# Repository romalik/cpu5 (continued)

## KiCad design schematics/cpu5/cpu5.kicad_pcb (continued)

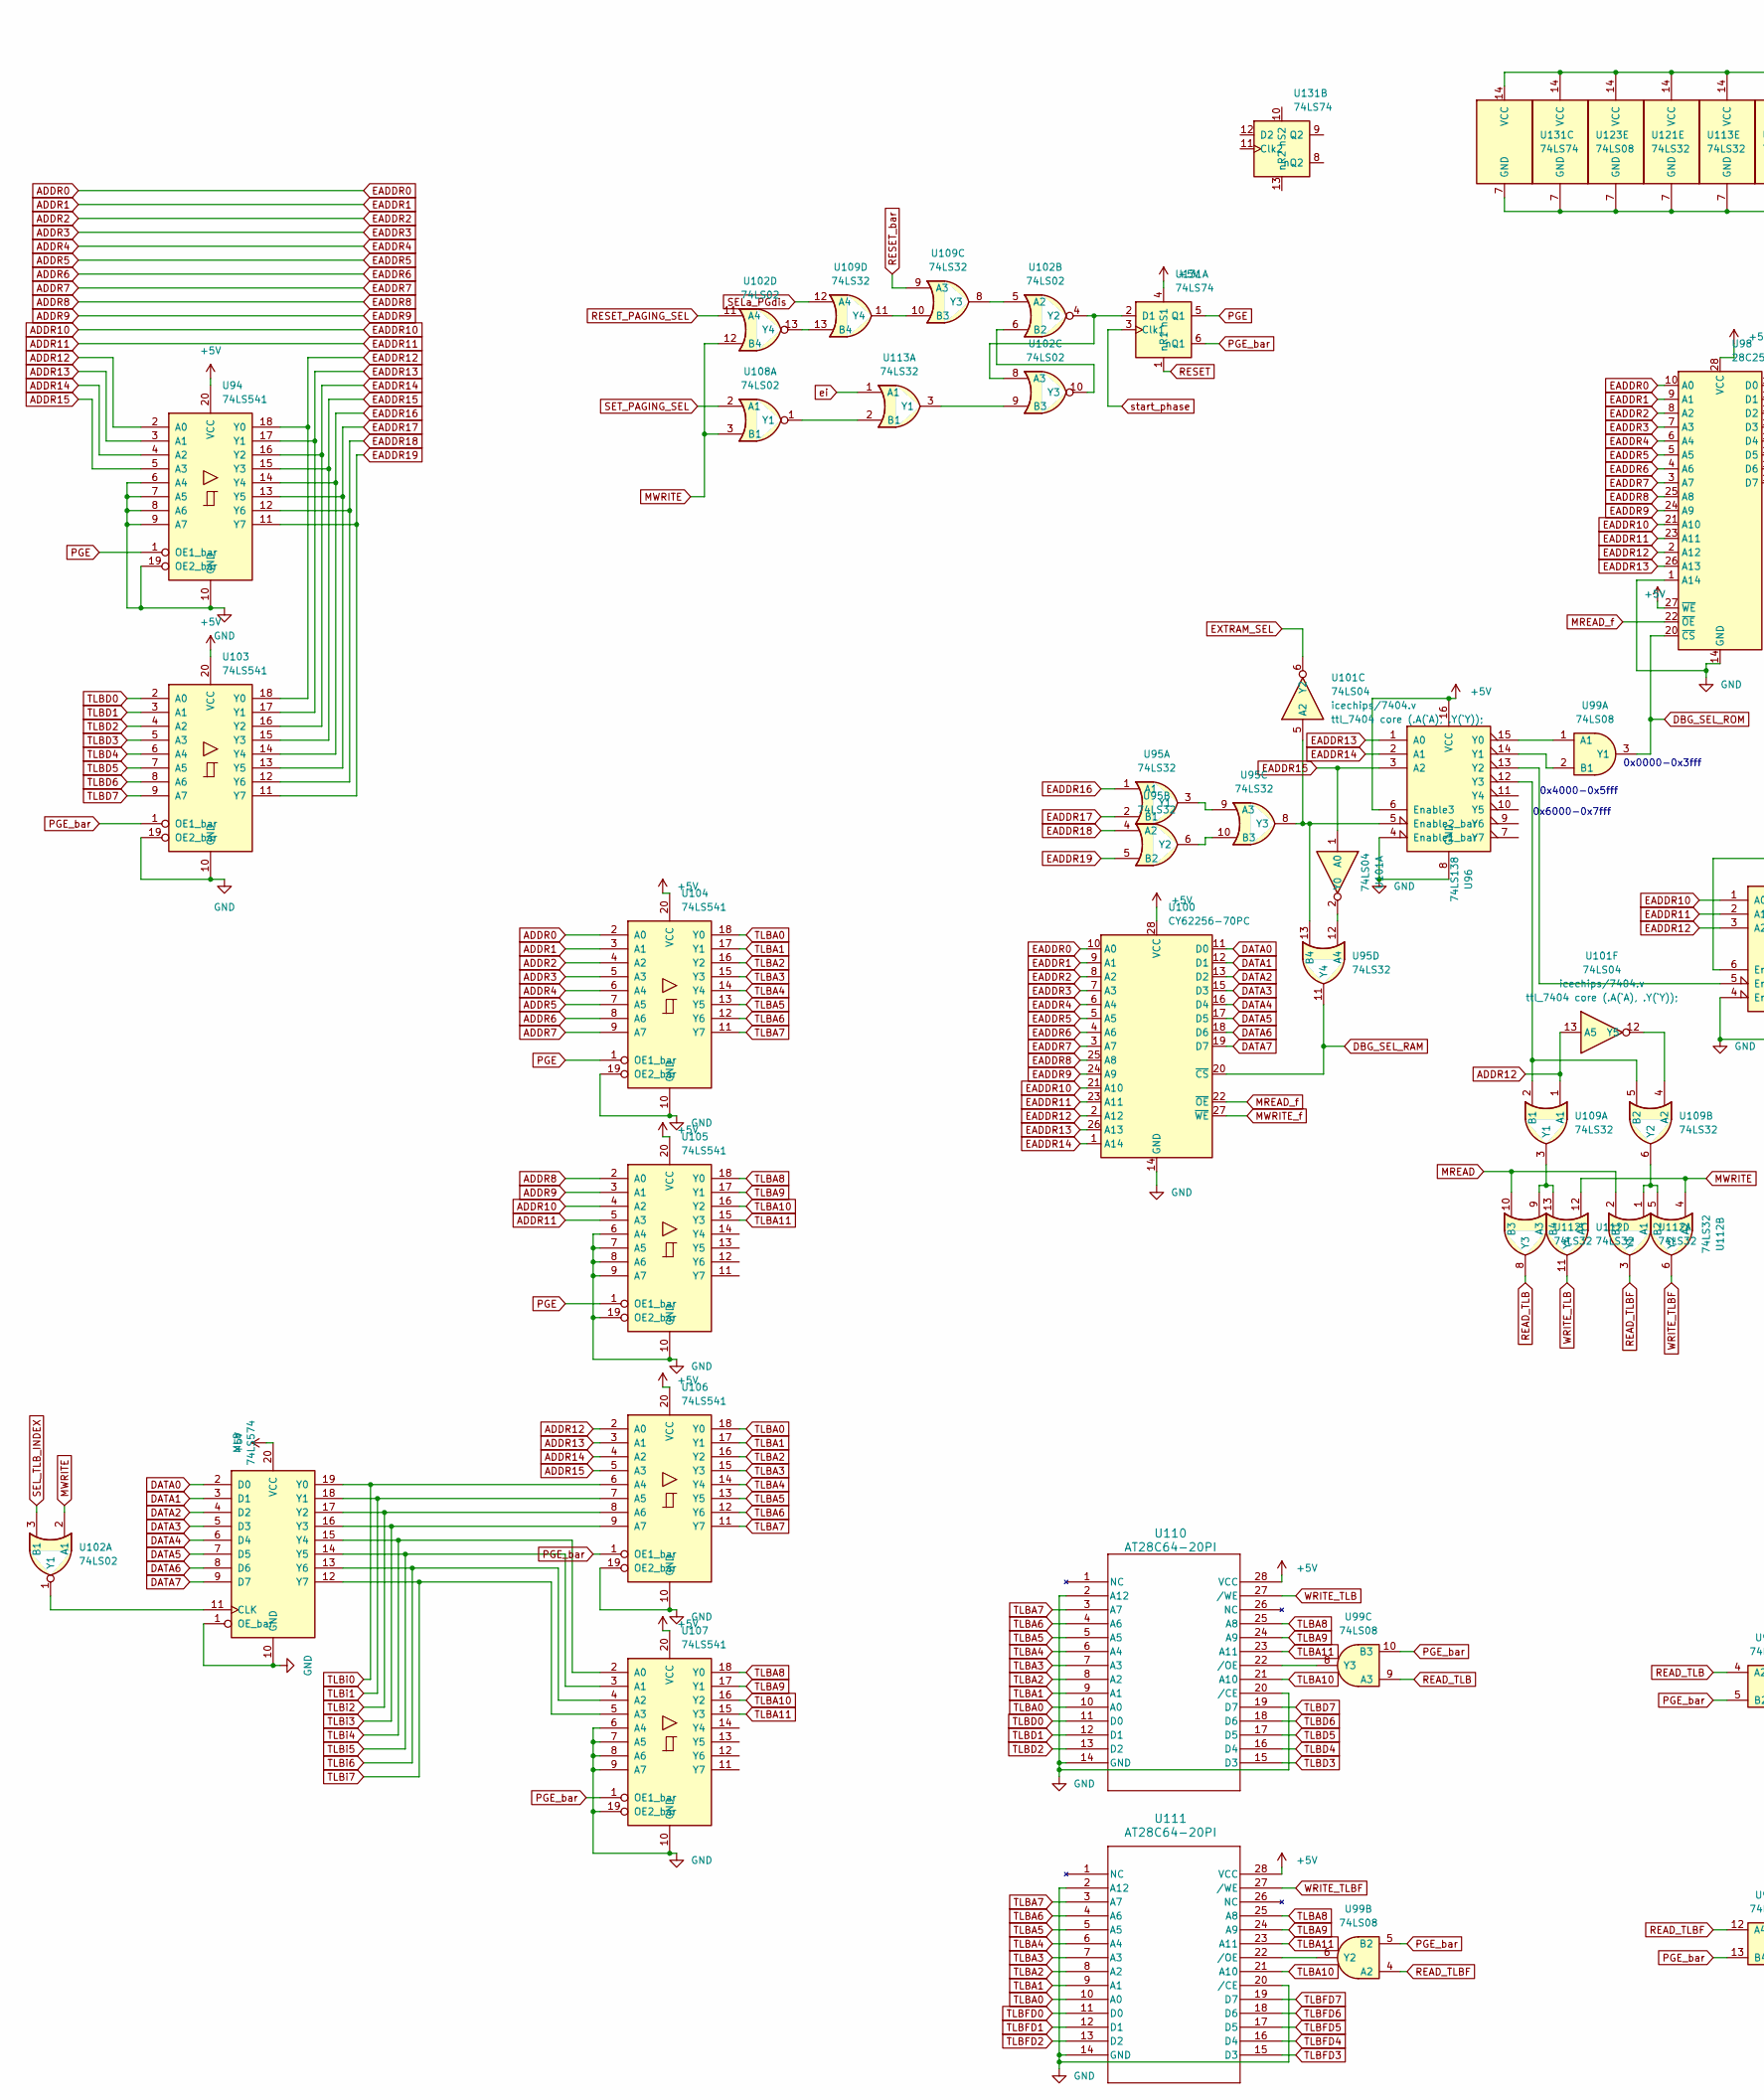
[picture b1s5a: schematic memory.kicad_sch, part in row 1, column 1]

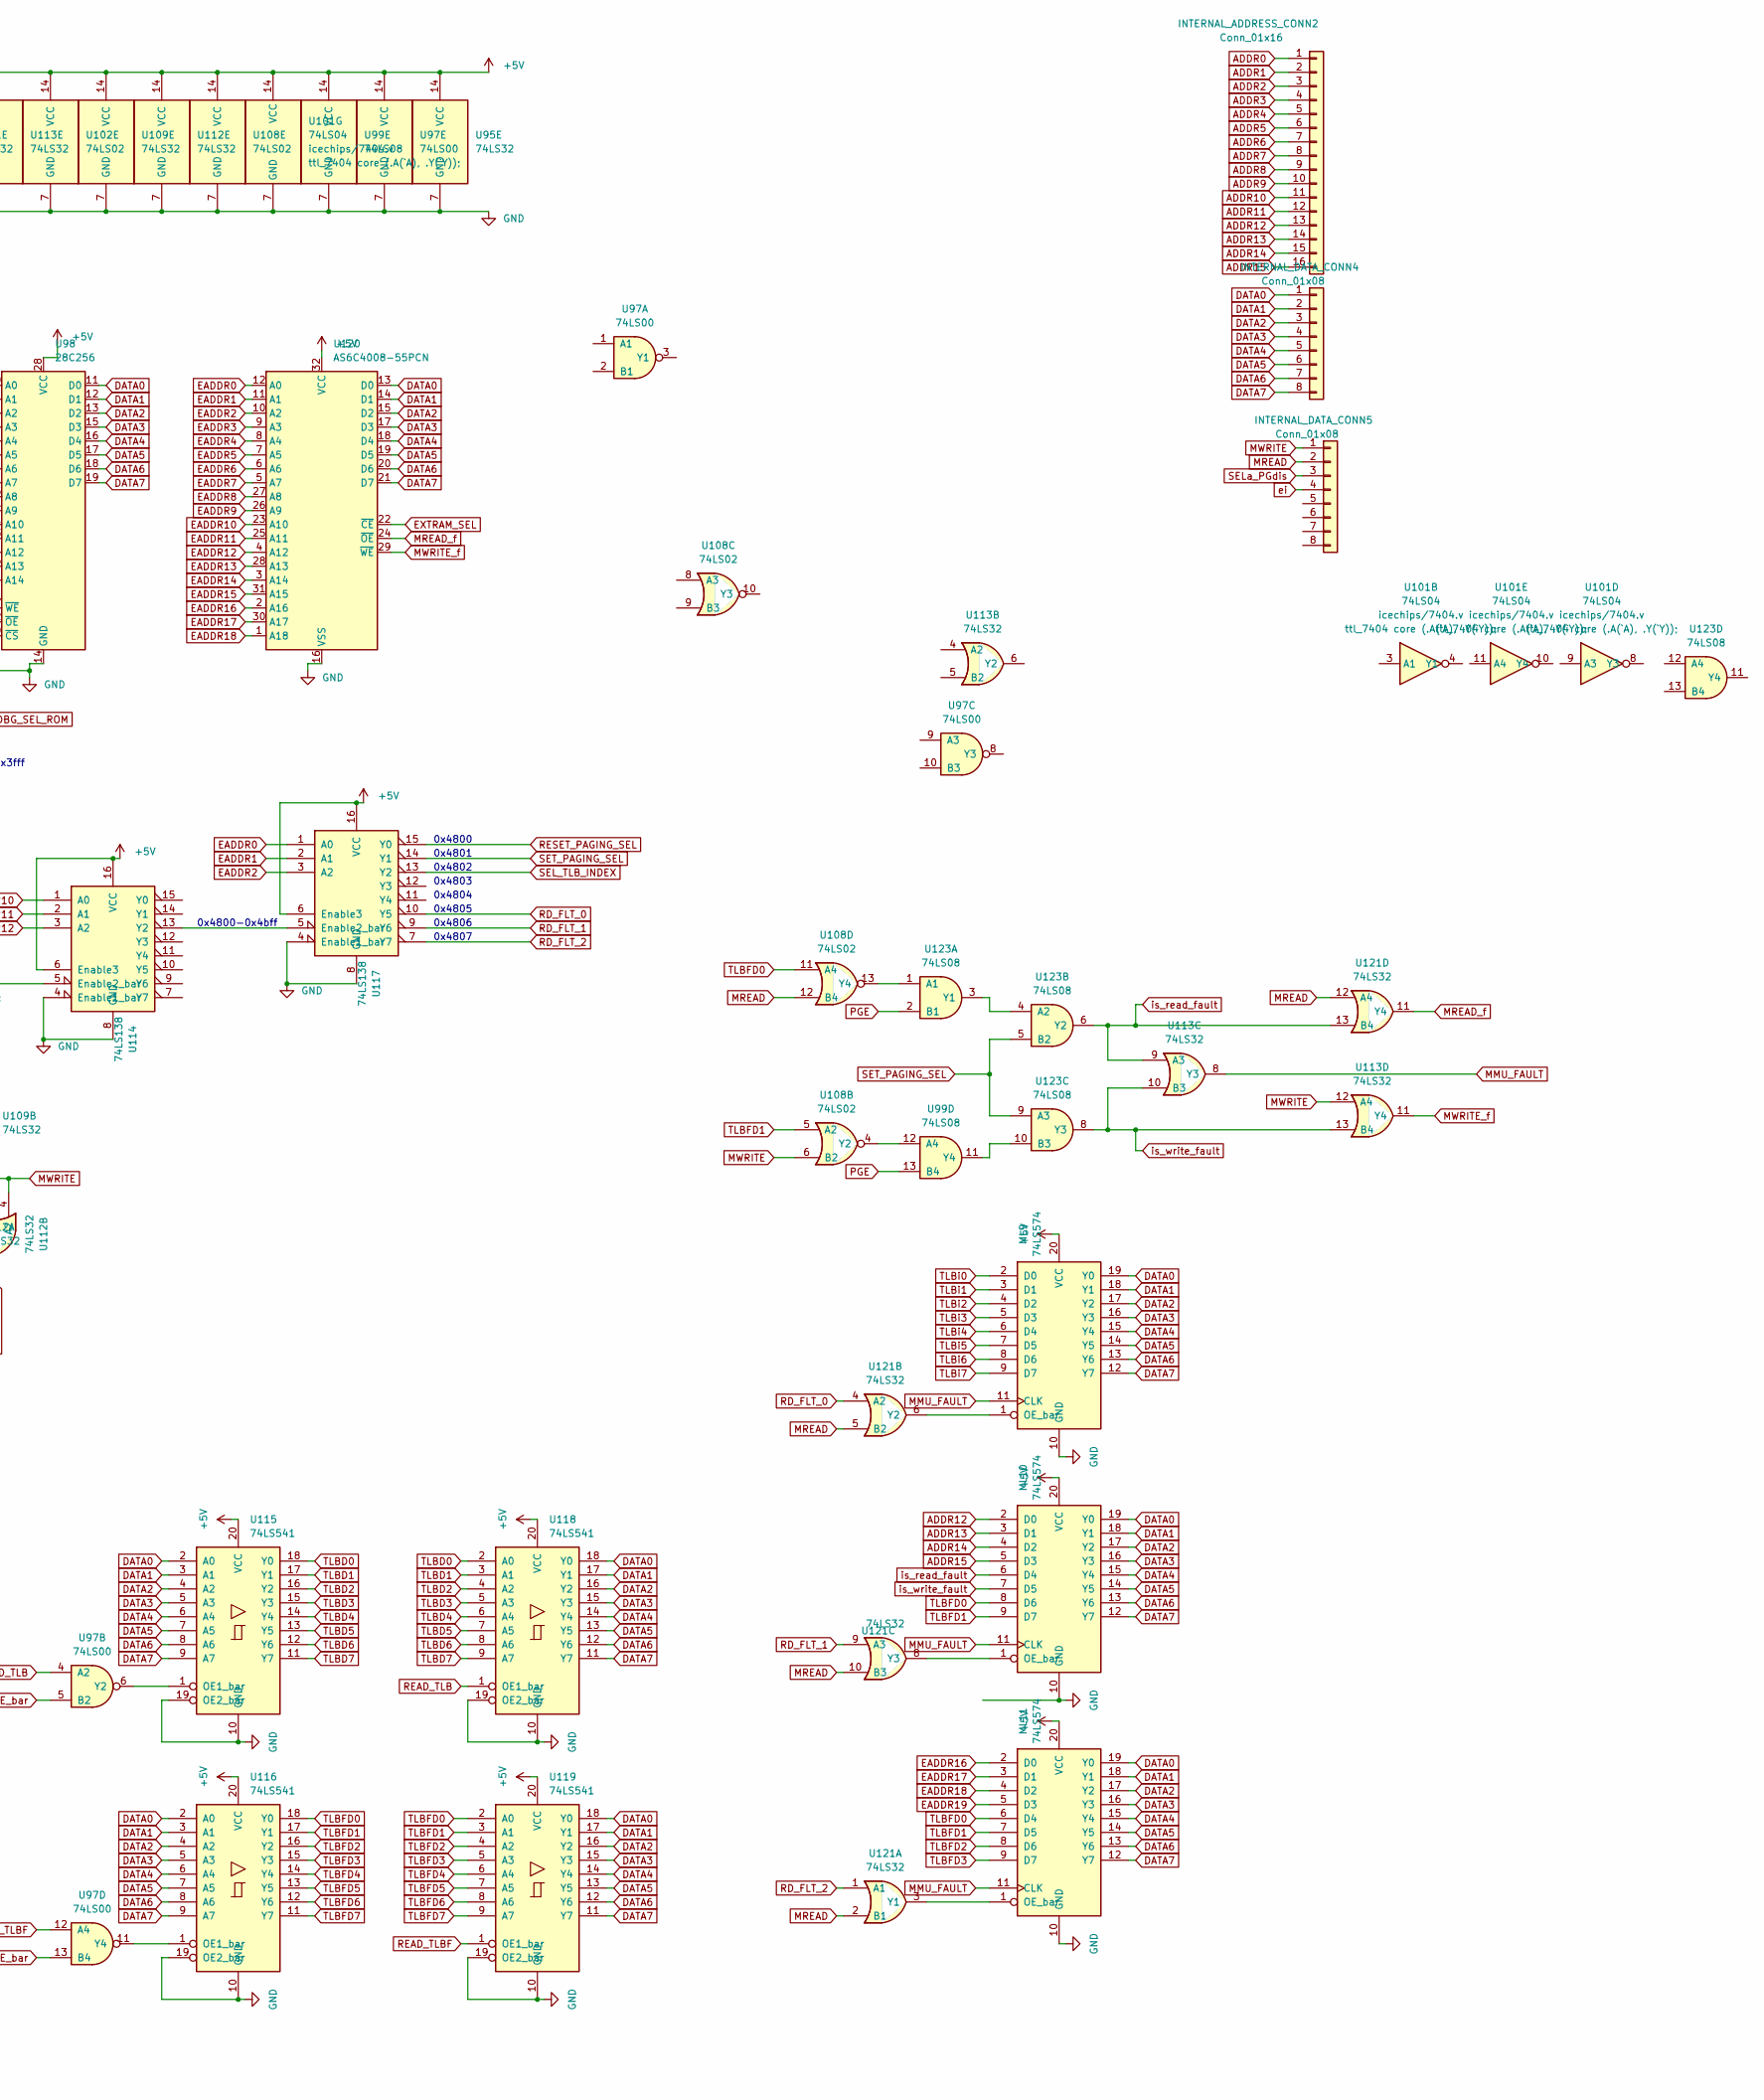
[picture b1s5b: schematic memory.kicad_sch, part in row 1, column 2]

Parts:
INTERNAL_ADDRESS_CONN2: Conn_01x16; PinHeader_1x16_P2.54mm_Vertical
INTERNAL_DATA_CONN4, INTERNAL_DATA_CONN5: Conn_01x08; PinHeader_1x08_P2.54mm_Vertical
ML8, ML9, ML10, ML11: 74LS574; DIP-20_W7.62mm
U94, U103, U104, U105, U106, U107, U115, U116, U118, U119: 74LS541; DIP-20_W7.62mm
U95, U109, U112, U113, U121: 74LS32; DIP-14_W7.62mm
U96, U114, U117: 74LS138; DIP-16_W7.62mm
U97: 74LS00; DIP-14_W7.62mm
U98: 28C256; DIP-28_W15.24mm
U99, U123: 74LS08; DIP-14_W7.62mm
U100: CY62256-70PC; DIP-28_W15.24mm
U101: 74LS04; DIP-14_W7.62mm
U102, U108: 74LS02; DIP-14_W7.62mm
U110, U111: AT28C64-20PI; DIP-28_W7.62mm
U120: AS6C4008-55PCN; DIP-32_W15.24mm
U131: 74LS74; DIP-14_W7.62mm

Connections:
+5V: ML8.20 (VCC), ML9.20 (VCC), ML10.20 (VCC), ML11.20 (VCC), U94.20 (VCC), U95.14 (VCC), U96.6 (Enable3), U96.16 (VCC), U97.14 (VCC), U98.27 (~WE), U98.28 (VCC), U99.14 (VCC), U100.28 (VCC), U101.14 (VCC), U102.14 (VCC), U103.20 (VCC), U104.20 (VCC), U105.20 (VCC), U106.20 (VCC), U107.20 (VCC), U108.14 (VCC), U109.14 (VCC), U110.28 (VCC), U111.28 (VCC), U112.14 (VCC), U113.14 (VCC), U114.6 (Enable3), U114.16 (VCC), U115.20 (VCC), U116.20 (VCC), U117.6 (Enable3), U117.16 (VCC), U118.20 (VCC), U119.20 (VCC), U120.32 (VCC), U121.14 (VCC), U123.14 (VCC), U131.4 (nS1), U131.14 (VCC); also elsewhere on the board
ADDR0: INTERNAL_ADDRESS_CONN2.1, U98.10 (A0), U100.10 (A0), U104.2 (A0), U117.1 (A0), U120.12 (A0); also elsewhere on the board
ADDR1: INTERNAL_ADDRESS_CONN2.2, U98.9 (A1), U100.9 (A1), U104.3 (A1), U117.2 (A1), U120.11 (A1); also elsewhere on the board
ADDR2: INTERNAL_ADDRESS_CONN2.3, U98.8 (A2), U100.8 (A2), U104.4 (A2), U117.3 (A2), U120.10 (A2); also elsewhere on the board
ADDR3: INTERNAL_ADDRESS_CONN2.4, U98.7 (A3), U100.7 (A3), U104.5 (A3), U120.9 (A3); also elsewhere on the board
ADDR4: INTERNAL_ADDRESS_CONN2.5, U98.6 (A4), U100.6 (A4), U104.6 (A4), U120.8 (A4); also elsewhere on the board
ADDR5: INTERNAL_ADDRESS_CONN2.6, U98.5 (A5), U100.5 (A5), U104.7 (A5), U120.7 (A5); also elsewhere on the board
ADDR6: INTERNAL_ADDRESS_CONN2.7, U98.4 (A6), U100.4 (A6), U104.8 (A6), U120.6 (A6); also elsewhere on the board
ADDR7: INTERNAL_ADDRESS_CONN2.8, U98.3 (A7), U100.3 (A7), U104.9 (A7), U120.5 (A7); also elsewhere on the board
ADDR8: INTERNAL_ADDRESS_CONN2.9, U98.25 (A8), U100.25 (A8), U105.2 (A0), U120.27 (A8); also elsewhere on the board
ADDR9: INTERNAL_ADDRESS_CONN2.10, U98.24 (A9), U100.24 (A9), U105.3 (A1), U120.26 (A9); also elsewhere on the board
ADDR10: INTERNAL_ADDRESS_CONN2.11, U98.21 (A10), U100.21 (A10), U105.4 (A2), U114.1 (A0), U120.23 (A10); also elsewhere on the board
ADDR11: INTERNAL_ADDRESS_CONN2.12, U98.23 (A11), U100.23 (A11), U105.5 (A3), U114.2 (A1), U120.25 (A11); also elsewhere on the board
ADDR12: INTERNAL_ADDRESS_CONN2.13, ML10.2 (D0), U94.2 (A0), U101.13 (A5), U106.2 (A0), U109.1 (A1); also elsewhere on the board
ADDR13: INTERNAL_ADDRESS_CONN2.14, ML10.3 (D1), U94.3 (A1), U106.3 (A1); also elsewhere on the board
ADDR14: INTERNAL_ADDRESS_CONN2.15, ML10.4 (D2), U94.4 (A2), U106.4 (A2); also elsewhere on the board
ADDR15: INTERNAL_ADDRESS_CONN2.16, ML10.5 (D3), U94.5 (A3), U106.5 (A3); also elsewhere on the board
DATA0: INTERNAL_DATA_CONN4.1, ML8.2 (D0), ML9.19 (Y0), ML10.19 (Y0), ML11.19 (Y0), U98.11 (D0), U100.11 (D0), U115.2 (A0), U116.2 (A0), U118.18 (Y0), U119.18 (Y0), U120.13 (D0); also elsewhere on the board
DATA1: INTERNAL_DATA_CONN4.2, ML8.3 (D1), ML9.18 (Y1), ML10.18 (Y1), ML11.18 (Y1), U98.12 (D1), U100.12 (D1), U115.3 (A1), U116.3 (A1), U118.17 (Y1), U119.17 (Y1), U120.14 (D1); also elsewhere on the board
DATA2: INTERNAL_DATA_CONN4.3, ML8.4 (D2), ML9.17 (Y2), ML10.17 (Y2), ML11.17 (Y2), U98.13 (D2), U100.13 (D2), U115.4 (A2), U116.4 (A2), U118.16 (Y2), U119.16 (Y2), U120.15 (D2); also elsewhere on the board
DATA3: INTERNAL_DATA_CONN4.4, ML8.5 (D3), ML9.16 (Y3), ML10.16 (Y3), ML11.16 (Y3), U98.15 (D3), U100.15 (D3), U115.5 (A3), U116.5 (A3), U118.15 (Y3), U119.15 (Y3), U120.17 (D3); also elsewhere on the board
DATA4: INTERNAL_DATA_CONN4.5, ML8.6 (D4), ML9.15 (Y4), ML10.15 (Y4), ML11.15 (Y4), U98.16 (D4), U100.16 (D4), U115.6 (A4), U116.6 (A4), U118.14 (Y4), U119.14 (Y4), U120.18 (D4); also elsewhere on the board
DATA5: INTERNAL_DATA_CONN4.6, ML8.7 (D5), ML9.14 (Y5), ML10.14 (Y5), ML11.14 (Y5), U98.17 (D5), U100.17 (D5), U115.7 (A5), U116.7 (A5), U118.13 (Y5), U119.13 (Y5), U120.19 (D5); also elsewhere on the board
DATA6: INTERNAL_DATA_CONN4.7, ML8.8 (D6), ML9.13 (Y6), ML10.13 (Y6), ML11.13 (Y6), U98.18 (D6), U100.18 (D6), U115.8 (A6), U116.8 (A6), U118.12 (Y6), U119.12 (Y6), U120.20 (D6); also elsewhere on the board
DATA7: INTERNAL_DATA_CONN4.8, ML8.9 (D7), ML9.12 (Y7), ML10.12 (Y7), ML11.12 (Y7), U98.19 (D7), U100.19 (D7), U115.9 (A7), U116.9 (A7), U118.11 (Y7), U119.11 (Y7), U120.21 (D7); also elsewhere on the board
DBG_SEL_RAM: U95.11 (Y4), U100.20 (~CS)
DBG_SEL_ROM: U98.20 (~CS), U99.3 (Y1)
EADDR12: U94.18 (Y0), U98.2 (A12), U100.2 (A12), U103.18 (Y0), U114.3 (A2), U120.4 (A12)
EADDR13: U94.17 (Y1), U96.1 (A0), U98.26 (A13), U100.26 (A13), U103.17 (Y1), U120.28 (A13)
EADDR14: U94.16 (Y2), U96.2 (A1), U100.1 (A14), U103.16 (Y2), U120.3 (A14)
EADDR15: U94.15 (Y3), U96.3 (A2), U101.1 (A0), U103.15 (Y3), U120.31 (A15)
EADDR16: ML11.2 (D0), U94.14 (Y4), U95.1 (A1), U103.14 (Y4), U120.2 (A16)
EADDR17: ML11.3 (D1), U94.13 (Y5), U95.2 (B1), U103.13 (Y5), U120.30 (A17)
EADDR18: ML11.4 (D2), U94.12 (Y6), U95.4 (A2), U103.12 (Y6), U120.1 (A18)
EADDR19: ML11.5 (D3), U94.11 (Y7), U95.5 (B2), U103.11 (Y7)
EXTRAM_SEL: U101.6 (Y2), U120.22 (~CE)
GND: ML8.1 (OE_bar), ML8.10 (GND), ML9.10 (GND), ML10.10 (GND), ML11.10 (GND), U94.6 (A4), U94.7 (A5), U94.8 (A6), U94.9 (A7), U94.10 (GND), U94.19 (OE2_bar), U95.7 (GND), U96.4 (Enable1_bar), U96.8 (GND), U97.7 (GND), U98.1 (A14), U98.14 (GND), U99.7 (GND), U100.14 (GND), U101.7 (GND), U102.7 (GND), U103.10 (GND), U103.19 (OE2_bar), U104.10 (GND), U104.19 (OE2_bar), U105.6 (A4), U105.7 (A5), U105.8 (A6), U105.9 (A7), U105.10 (GND), U105.19 (OE2_bar), U106.10 (GND), U106.19 (OE2_bar), U107.6 (A4), U107.7 (A5), U107.8 (A6), U107.9 (A7), U107.10 (GND), U107.19 (OE2_bar), U108.7 (GND), U109.7 (GND), U110.2 (A12), U110.14 (GND), U110.20 (/CE), U111.2 (A12), U111.14 (GND), U111.20 (/CE), U112.7 (GND), U113.7 (GND), U114.4 (Enable1_bar), U114.8 (GND), U115.10 (GND), U115.19 (OE2_bar), U116.10 (GND), U116.19 (OE2_bar), U117.4 (Enable1_bar), U117.8 (GND), U118.10 (GND), U118.19 (OE2_bar), U119.10 (GND), U119.19 (OE2_bar), U120.16 (VSS), U121.7 (GND), U123.7 (GND), U131.7 (GND); also elsewhere on the board
MMU_FAULT: ML9.11 (CLK), ML10.11 (CLK), ML11.11 (CLK), U113.8 (Y3); also elsewhere on the board
MREAD: INTERNAL_DATA_CONN5.2, U108.12 (B4), U112.2 (B1), U112.10 (B3), U121.2 (B1), U121.5 (B2), U121.10 (B3), U121.12 (A4); also elsewhere on the board
MREAD_f: U98.22 (~OE), U100.22 (~OE), U120.24 (~OE), U121.11 (Y4)
MWRITE: INTERNAL_DATA_CONN5.1, U102.2 (A1), U102.12 (B4), U108.3 (B1), U108.6 (B2), U112.4 (A2), U112.12 (A4), U113.12 (A4); also elsewhere on the board
MWRITE_f: U100.27 (~WE), U113.11 (Y4), U120.29 (~WE)
unnamed: ML8.11 (CLK), U102.1 (Y1)
unnamed: ML9.1 (OE_bar), U121.6 (Y2)
unnamed: ML10.1 (OE_bar), U121.8 (Y3)
unnamed: ML11.1 (OE_bar), U121.3 (Y1)
unnamed: U95.3 (Y1), U95.9 (A3)
unnamed: U95.6 (Y2), U95.10 (B3)
unnamed: U96.14 (Y1), U99.2 (B1)
unnamed: U96.15 (Y0), U99.1 (A1)
unnamed: U95.12 (A4), U101.2 (Y0)
unnamed: U95.8 (Y3), U95.13 (B4), U96.5 (Enable2_bar), U101.5 (A2)
unnamed: U101.12 (Y5), U109.4 (A2)
unnamed: U102.4 (Y2), U102.8 (A3), U131.2 (D1)
unnamed: U102.5 (A2), U109.8 (Y3)
unnamed: U102.9 (B3), U113.3 (Y1)
unnamed: U102.6 (B2), U102.10 (Y3)
unnamed: U102.13 (Y4), U109.13 (B4)
unnamed: U108.1 (Y1), U113.2 (B1)
unnamed: U99.12 (A4), U108.4 (Y2)
unnamed: U108.13 (Y4), U123.1 (A1)
unnamed: U96.12 (Y3), U109.2 (B1), U109.5 (B2)
unnamed: U109.3 (Y1), U112.9 (A3), U112.13 (B4)
unnamed: U109.6 (Y2), U112.1 (A1), U112.5 (B2)
unnamed: U109.10 (B3), U109.11 (Y4)
unnamed: U99.8 (Y3), U110.22 (/OE)
unnamed: U99.6 (Y2), U111.22 (/OE)
unnamed: U96.13 (Y2), U114.5 (Enable2_bar)
unnamed: U114.13 (Y2), U117.5 (Enable2_bar)
unnamed: U97.6 (Y2), U115.1 (OE1_bar)
unnamed: U97.11 (Y4), U116.1 (OE1_bar)
unnamed: U123.3 (Y1), U123.4 (A2)
unnamed: U99.11 (Y4), U123.10 (B3)
PGE: U94.1 (OE1_bar), U99.13 (B4), U104.1 (OE1_bar), U105.1 (OE1_bar), U123.2 (B1), U131.5 (Q1); also elsewhere on the board
PGE_bar: U97.5 (B2), U97.13 (B4), U99.5 (B2), U99.10 (B3), U103.1 (OE1_bar), U106.1 (OE1_bar), U107.1 (OE1_bar), U131.6 (nQ1)
RD_FLT_0: U117.10 (Y5), U121.4 (A2)
RD_FLT_1: U117.9 (Y6), U121.9 (A3)
RD_FLT_2: U117.7 (Y7), U121.1 (A1)
READ_TLB: U97.4 (A2), U99.9 (A3), U112.8 (Y3), U118.1 (OE1_bar)
READ_TLBF: U97.12 (A4), U99.4 (A2), U112.3 (Y1), U119.1 (OE1_bar)
RESET: U131.1 (nR1); also elsewhere on the board
RESET_PAGING_SEL: U102.11 (A4), U117.15 (Y0)
RESET_bar: U109.9 (A3); also elsewhere on the board
SEL_TLB_INDEX: U102.3 (B1), U117.13 (Y2)
SELa_PGdis: INTERNAL_DATA_CONN5.3, U109.12 (A4); also elsewhere on the board
SET_PAGING_SEL: U108.2 (A1), U117.14 (Y1), U123.5 (B2), U123.9 (A3)
TLBA0: U104.18 (Y0), U106.18 (Y0), U110.10 (A0), U111.10 (A0)
TLBA1: U104.17 (Y1), U106.17 (Y1), U110.9 (A1), U111.9 (A1)
TLBA2: U104.16 (Y2), U106.16 (Y2), U110.8 (A2), U111.8 (A2)
TLBA3: U104.15 (Y3), U106.15 (Y3), U110.7 (A3), U111.7 (A3)
TLBA4: U104.14 (Y4), U106.14 (Y4), U110.6 (A4), U111.6 (A4)
TLBA5: U104.13 (Y5), U106.13 (Y5), U110.5 (A5), U111.5 (A5)
TLBA6: U104.12 (Y6), U106.12 (Y6), U110.4 (A6), U111.4 (A6)
TLBA7: U104.11 (Y7), U106.11 (Y7), U110.3 (A7), U111.3 (A7)
TLBA8: U105.18 (Y0), U107.18 (Y0), U110.25 (A8), U111.25 (A8)
TLBA9: U105.17 (Y1), U107.17 (Y1), U110.24 (A9), U111.24 (A9)
TLBA10: U105.16 (Y2), U107.16 (Y2), U110.21 (A10), U111.21 (A10)
TLBA11: U105.15 (Y3), U107.15 (Y3), U110.23 (A11), U111.23 (A11)
TLBD0: U103.2 (A0), U110.11 (D0), U115.18 (Y0), U118.2 (A0)
TLBD1: U103.3 (A1), U110.12 (D1), U115.17 (Y1), U118.3 (A1)
TLBD2: U103.4 (A2), U110.13 (D2), U115.16 (Y2), U118.4 (A2)
TLBD3: U103.5 (A3), U110.15 (D3), U115.15 (Y3), U118.5 (A3)
TLBD4: U103.6 (A4), U110.16 (D4), U115.14 (Y4), U118.6 (A4)
TLBD5: U103.7 (A5), U110.17 (D5), U115.13 (Y5), U118.7 (A5)
TLBD6: U103.8 (A6), U110.18 (D6), U115.12 (Y6), U118.8 (A6)
TLBD7: U103.9 (A7), U110.19 (D7), U115.11 (Y7), U118.9 (A7)
TLBFD0: ML10.8 (D6), ML11.6 (D4), U108.11 (A4), U111.11 (D0), U116.18 (Y0), U119.2 (A0)
TLBFD1: ML10.9 (D7), ML11.7 (D5), U108.5 (A2), U111.12 (D1), U116.17 (Y1), U119.3 (A1)
TLBFD2: ML11.8 (D6), U111.13 (D2), U116.16 (Y2), U119.4 (A2)
TLBFD3: ML11.9 (D7), U111.15 (D3), U116.15 (Y3), U119.5 (A3)
TLBFD4: U111.16 (D4), U116.14 (Y4), U119.6 (A4)
TLBFD5: U111.17 (D5), U116.13 (Y5), U119.7 (A5)
TLBFD6: U111.18 (D6), U116.12 (Y6), U119.8 (A6)
TLBFD7: U111.19 (D7), U116.11 (Y7), U119.9 (A7)
TLBi0: ML8.19 (Y0), ML9.2 (D0), U106.6 (A4)
TLBi1: ML8.18 (Y1), ML9.3 (D1), U106.7 (A5)
TLBi2: ML8.17 (Y2), ML9.4 (D2), U106.8 (A6)
TLBi3: ML8.16 (Y3), ML9.5 (D3), U106.9 (A7)
TLBi4: ML8.15 (Y4), ML9.6 (D4), U107.2 (A0)
TLBi5: ML8.14 (Y5), ML9.7 (D5), U107.3 (A1)
TLBi6: ML8.13 (Y6), ML9.8 (D6), U107.4 (A2)
TLBi7: ML8.12 (Y7), ML9.9 (D7), U107.5 (A3)
WRITE_TLB: U110.27 (/WE), U112.11 (Y4)
WRITE_TLBF: U111.27 (/WE), U112.6 (Y2)
ei: INTERNAL_DATA_CONN5.4, U113.1 (A1); also elsewhere on the board
is_read_fault: ML10.6 (D4), U113.9 (A3), U121.13 (B4), U123.6 (Y2)
is_write_fault: ML10.7 (D5), U113.10 (B3), U113.13 (B4), U123.8 (Y3)
start_phase: U131.3 (Clk1); also elsewhere on the board

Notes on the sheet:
0x4807
0x4000-0x5fff
0x0000-0x3fff
0x4806
0x4805
0x4801
0x4804
0x6000-0x7fff
0x4800-0x4bff
0x4800
0x4803
0x4802

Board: 2 copper layers, 187 parts (0 on the bottom side), 567 nets, no tracks yet.

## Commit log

2022-05-01 snake initial
2024-03-27 new iteration in Digital
2024-03-27 intr works
2024-03-28 iret works
2024-04-03 + TLB, ISR
2024-04-03 ISR works correctly
2024-04-03 cleanup
2024-04-05 + SmallerC with rlcpu codegen
2024-04-05 + x++
2024-04-05 flags in decoder
2024-04-06 flags, [m+imm]
2024-04-07 c compiler wip
2024-04-07 offset rework
2024-04-07 three address works
2024-04-07 compiler alpha ready
2024-04-07 build system
2024-04-08 c code runs
2024-04-08 fix last commit
2024-04-09 varoius flags bugs fixed
2024-04-10 another iteration of fixing flags
2024-04-12 before radical size optimizaiton
2024-04-17 +movw X
2024-04-17 + push/pop r
2024-04-17 popw/pushw
2024-04-17 opt tokNumInt
2024-04-18 tests work
2024-04-18 snake kinda works
2024-04-20 trenary wip
2024-04-20 trenary seems to work
2024-04-20 install generates all binaries
2024-05-08 + Baselibc
2024-05-09 fixes
2024-05-09 baselibc compiles
2024-05-09 missing files
2024-05-09 MMU Worksgit status
2024-05-10 interrupts from C
2024-05-10 + uart buffer, syscalls
2024-05-13 kernel works
2024-05-13 load apps
2024-06-06 add W,Y,Z WIP
2025-03-20 sorta task switching
2025-03-21 proper task switching
2025-03-21 app start at 0x0000
2025-03-21 half-stable multitask
2025-03-22 more refactoring
2025-08-27 +kicad +verilog
2025-08-27 microcode rom works
2025-08-30 nop works
2025-08-30 C++ verilator works
2025-08-31 address marching with PC
2025-08-31 marching works
2025-09-02 verilator works, loop program works
2025-09-07 os + ints work, ZF issue
2025-09-07 flags ok
2025-09-08 Multithread + paging!
2025-09-08 tick tweak
2025-09-08 speedup
2025-09-09 start faults
2025-09-09 faults seem to work
2025-09-10 Page faults work
2025-09-10 perf experiments
2025-09-12 cmake pipeline
2025-09-12 umake
2025-09-13 logic simulator wip
2025-09-13 l_sim kinda works
2025-09-14 interrupts in lsim
2025-09-14 paging in lsim wip
2025-09-14 user space works in lsim
2025-09-15 + clock sim
2025-09-16 faults fixed
2025-09-16 ugly fault impl in l_sim
2025-09-16 sys_exec()
2025-09-19 + chibicc initial
2025-09-20 init chibicc cpu5 codegen
2025-09-20 wip on chibicc codegen
